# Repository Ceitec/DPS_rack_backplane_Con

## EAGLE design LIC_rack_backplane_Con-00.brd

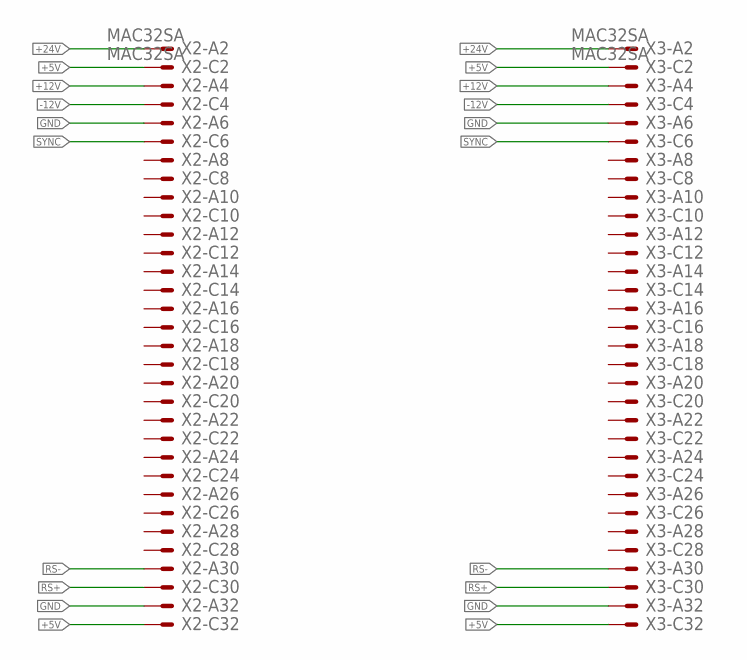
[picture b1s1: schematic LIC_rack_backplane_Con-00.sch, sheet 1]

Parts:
X2, X3: MAC32SA

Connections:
+5V: X2.C2, X2.C32, X3.C2, X3.C32; also elsewhere on the board
+12V: X2.A4, X3.A4
+24V: X2.A2, X3.A2; also elsewhere on the board
-12V: X2.C4, X3.C4
GND: X2.A6, X2.A32, X3.A6, X3.A32; also elsewhere on the board
RS+: X2.C30, X3.C30
RS-: X2.A30, X3.A30
SYNC: X2.C6, X3.C6

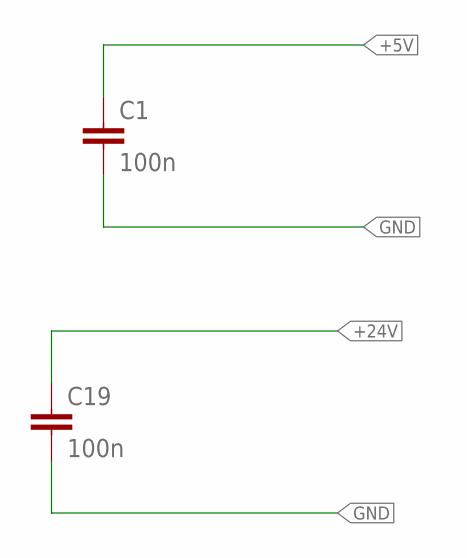
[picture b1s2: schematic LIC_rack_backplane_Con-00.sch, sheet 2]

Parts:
C1, C19: 100n; C1206

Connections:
+5V: C1.1; also elsewhere on the board
+24V: C19.1; also elsewhere on the board
GND: C1.2, C19.2; also elsewhere on the board

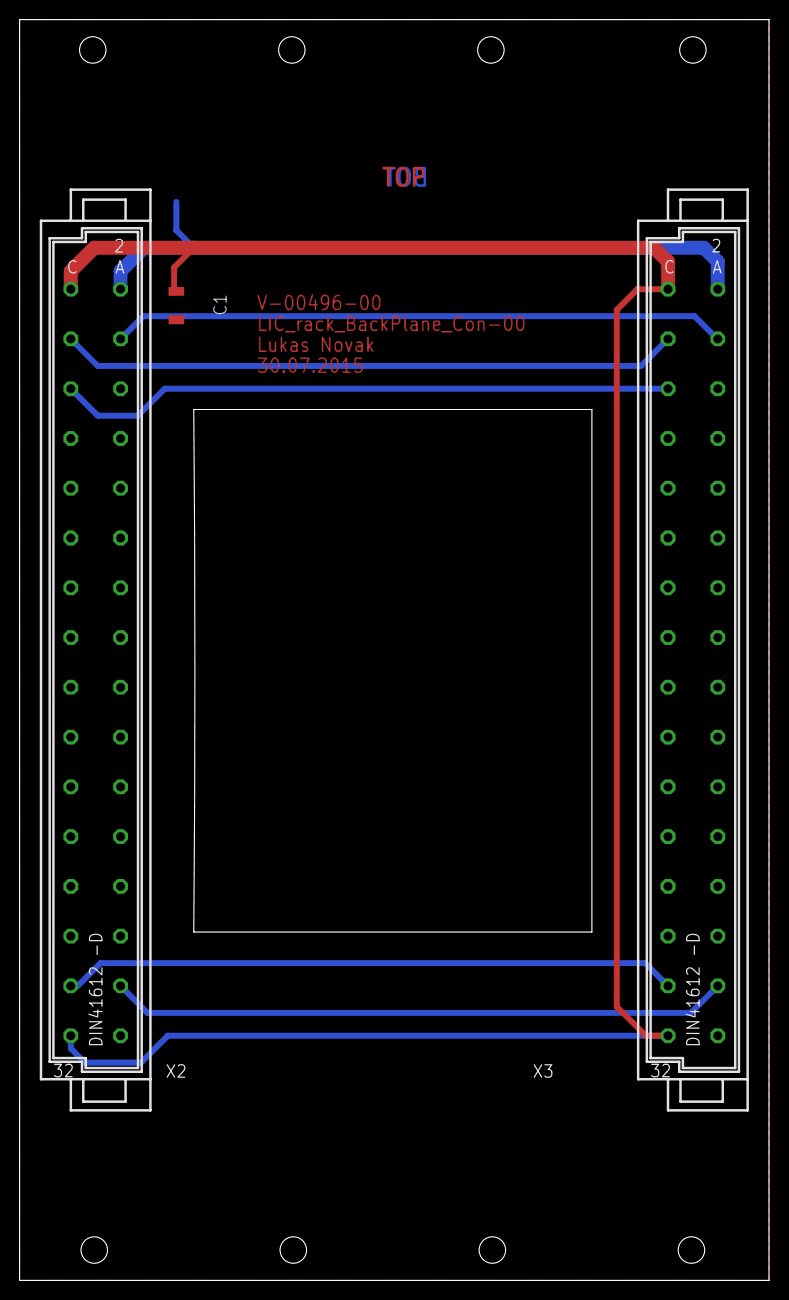
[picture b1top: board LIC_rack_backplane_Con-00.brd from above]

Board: 2 copper layers, 76.5 x 128.7 mm, 4 parts (1 on the bottom side), 8 nets.

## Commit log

2015-08-11 :octocat: Added .gitattributes & .gitignore files
2015-08-11 BackPlane Connect
    Propojovací díl k backplaně
2015-08-11 Pridani zakazanych koncovek
